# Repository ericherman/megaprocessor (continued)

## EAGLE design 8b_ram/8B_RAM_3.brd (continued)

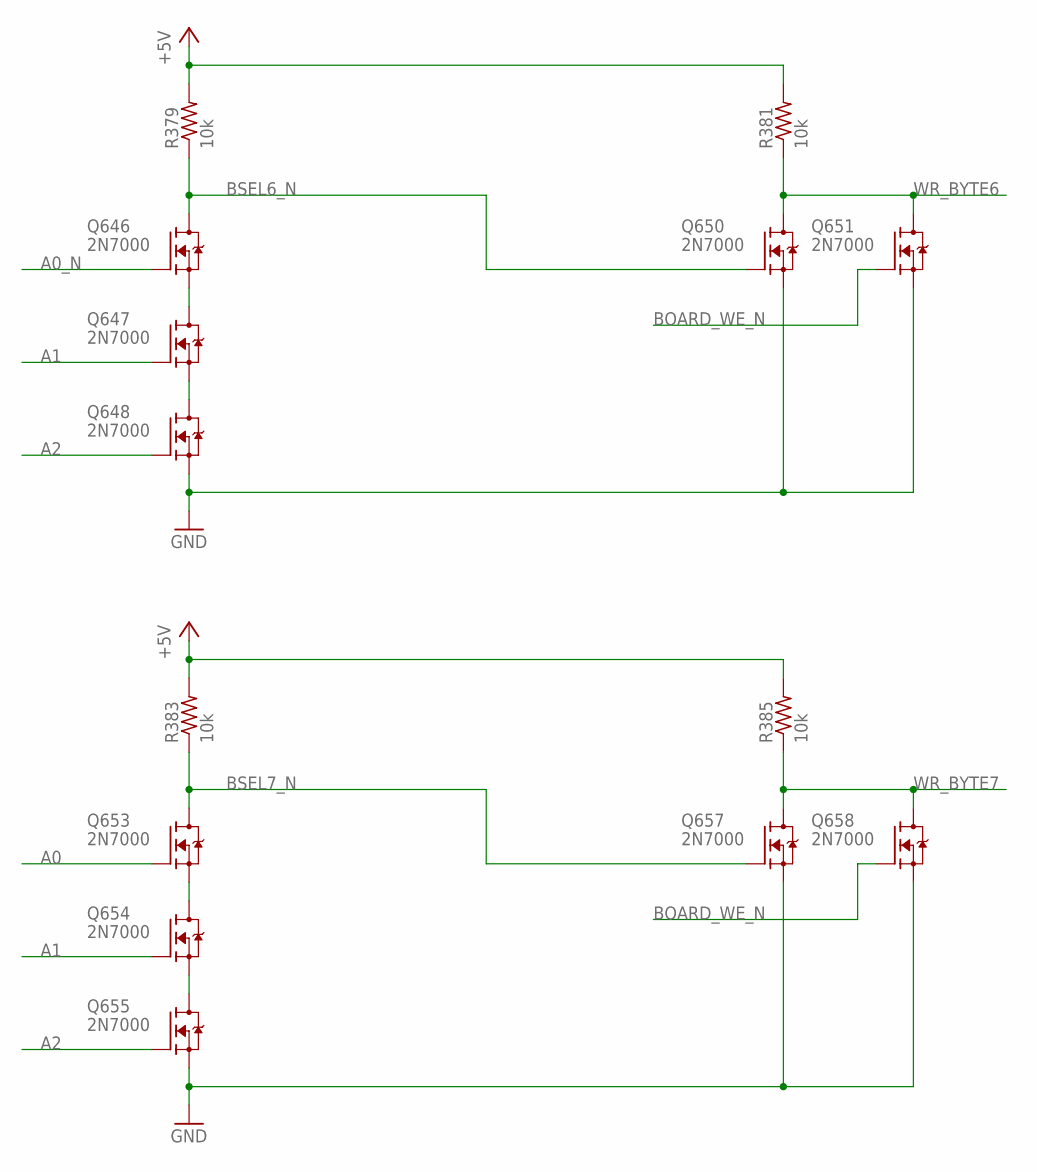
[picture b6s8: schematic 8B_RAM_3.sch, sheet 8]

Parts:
Q646, Q647, Q648, Q650, Q651, Q653, Q654, Q655, Q657, Q658: 2N7000; TO92-DGS
R379, R381, R383, R385: 10k; R_P2INCH

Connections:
+5V: R379.2, R381.2, R383.2, R385.2; also elsewhere on the board
A0: Q653.G; also elsewhere on the board
A0_N: Q646.G; also elsewhere on the board
A1: Q647.G, Q654.G; also elsewhere on the board
A2: Q648.G, Q655.G; also elsewhere on the board
BOARD_WE_N: Q651.G, Q658.G; also elsewhere on the board
BSEL6_N: Q646.D, Q650.G, R379.1; also elsewhere on the board
BSEL7_N: Q653.D, Q657.G, R383.1; also elsewhere on the board
GND: Q648.S, Q650.S, Q651.S, Q655.S, Q657.S, Q658.S; also elsewhere on the board
unnamed: Q646.S, Q647.D
unnamed: Q647.S, Q648.D
unnamed: Q653.S, Q654.D
unnamed: Q654.S, Q655.D
WR_BYTE6: Q650.D, Q651.D, R381.1; also elsewhere on the board
WR_BYTE7: Q657.D, Q658.D, R385.1; also elsewhere on the board

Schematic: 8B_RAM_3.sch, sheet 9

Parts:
D1, D2: L-1334SRT; LED3MM
Q1, Q2, Q3, Q4, Q5, Q6, Q7, Q8, Q9, Q10, Q11, Q12, Q13, Q14, Q15, Q16, Q17, Q18, Q686, Q687: 2N7000; TO92-DGS
R1, R2, R3, R4, R6, R7, R8, R9, R415, R416: 10k; R_P2INCH
R5, R10: 470; R_P2INCH

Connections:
+5V: D1.A, D2.A, R1.2, R2.2, R3.2, R4.2, R6.2, R7.2, R8.2, R9.2, R415.2, R416.2; also elsewhere on the board
B0_0: Q5.G, Q8.D, R4.1, R5.1
B0_0_N: Q6.D, Q8.G, Q17.G, R3.1
B0_1: Q13.G, Q16.D, R9.1, R10.1
B0_1_N: Q14.D, Q16.G, Q18.G, R8.1
BSEL0_N: Q686.G, Q687.G; also elsewhere on the board
GND: Q1.S, Q3.S, Q5.S, Q7.S, Q9.S, Q11.S, Q13.S, Q15.S, Q17.S, Q18.S, Q686.S, Q687.S; also elsewhere on the board
unnamed: Q9.D, Q10.S
unnamed: Q7.D, Q8.S
unnamed: Q11.D, Q12.S
unnamed: Q13.D, Q14.S
unnamed: Q1.D, Q2.S
unnamed: Q3.D, Q4.S
unnamed: Q10.D, Q12.G, Q14.G, R6.1
unnamed: Q5.D, Q6.S
unnamed: Q12.D, Q15.G, R7.1
unnamed: D2.K (C), R10.2
unnamed: Q2.D, Q4.G, Q6.G, R1.1
unnamed: Q4.D, Q7.G, R2.1
unnamed: Q15.D, Q16.S
unnamed: D1.K (C), R5.2
RD_0_0: Q17.D, Q686.D, R415.1; also elsewhere on the board
RD_0_1: Q18.D, Q687.D, R416.1; also elsewhere on the board
WD0: Q2.G; also elsewhere on the board
WD1: Q10.G; also elsewhere on the board
WR_BYTE0: Q1.G, Q3.G, Q9.G, Q11.G; also elsewhere on the board

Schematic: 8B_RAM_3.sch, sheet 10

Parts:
D5, D6: L-1334SRT; LED3MM
Q37, Q38, Q39, Q40, Q41, Q42, Q43, Q44, Q45, Q46, Q47, Q48, Q49, Q50, Q51, Q52, Q53, Q54, Q688, Q689: 2N7000; TO92-DGS
R21, R22, R23, R24, R26, R27, R28, R29, R417, R418: 10k; R_P2INCH
R25, R30: 470; R_P2INCH

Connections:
+5V: D5.A, D6.A, R21.2, R22.2, R23.2, R24.2, R26.2, R27.2, R28.2, R29.2, R417.2, R418.2; also elsewhere on the board
B0_2: Q41.G, Q43.D, R24.1, R25.1
B0_2_N: Q42.D, Q43.G, Q53.G, R23.1
B0_3: Q49.G, Q51.D, R29.1, R30.1
B0_3_N: Q50.D, Q51.G, Q54.G, R28.1
BSEL0_N: Q688.G, Q689.G; also elsewhere on the board
GND: Q37.S, Q39.S, Q41.S, Q44.S, Q45.S, Q47.S, Q49.S, Q52.S, Q53.S, Q54.S, Q688.S, Q689.S; also elsewhere on the board
unnamed: Q37.D, Q38.S
unnamed: Q39.D, Q40.S
unnamed: Q41.D, Q42.S
unnamed: Q38.D, Q40.G, Q42.G, R21.1
unnamed: Q40.D, Q44.G, R22.1
unnamed: D5.K (C), R25.2
unnamed: Q43.S, Q44.D
unnamed: Q45.D, Q46.S
unnamed: Q47.D, Q48.S
unnamed: Q49.D, Q50.S
unnamed: Q46.D, Q48.G, Q50.G, R26.1
unnamed: Q48.D, Q52.G, R27.1
unnamed: D6.K (C), R30.2
unnamed: Q51.S, Q52.D
RD_0_2: Q53.D, Q688.D, R417.1; also elsewhere on the board
RD_0_3: Q54.D, Q689.D, R418.1; also elsewhere on the board
WD2: Q38.G; also elsewhere on the board
WD3: Q46.G; also elsewhere on the board
WR_BYTE0: Q37.G, Q39.G, Q45.G, Q47.G; also elsewhere on the board

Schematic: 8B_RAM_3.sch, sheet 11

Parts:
D7, D8: L-1334SRT; LED3MM
Q55, Q56, Q57, Q58, Q59, Q60, Q61, Q62, Q63, Q64, Q65, Q66, Q67, Q68, Q69, Q70, Q71, Q72, Q690, Q691: 2N7000; TO92-DGS
R31, R32, R33, R34, R36, R37, R38, R39, R419, R420: 10k; R_P2INCH
R35, R40: 470; R_P2INCH

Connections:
+5V: D7.A, D8.A, R31.2, R32.2, R33.2, R34.2, R36.2, R37.2, R38.2, R39.2, R419.2, R420.2; also elsewhere on the board
B0_4: Q59.G, Q61.D, R34.1, R35.1
B0_4_N: Q60.D, Q61.G, Q71.G, R33.1
B0_5: Q67.G, Q69.D, R39.1, R40.1
B0_5_N: Q68.D, Q69.G, Q72.G, R38.1
BSEL0_N: Q690.G, Q691.G; also elsewhere on the board
GND: Q55.S, Q57.S, Q59.S, Q62.S, Q63.S, Q65.S, Q67.S, Q70.S, Q71.S, Q72.S, Q690.S, Q691.S; also elsewhere on the board
unnamed: Q55.D, Q56.S
unnamed: Q57.D, Q58.S
unnamed: Q59.D, Q60.S
unnamed: Q56.D, Q58.G, Q60.G, R31.1
unnamed: Q58.D, Q62.G, R32.1
unnamed: D7.K (C), R35.2
unnamed: Q61.S, Q62.D
unnamed: Q63.D, Q64.S
unnamed: Q65.D, Q66.S
unnamed: Q67.D, Q68.S
unnamed: Q64.D, Q66.G, Q68.G, R36.1
unnamed: Q66.D, Q70.G, R37.1
unnamed: D8.K (C), R40.2
unnamed: Q69.S, Q70.D
RD_0_4: Q71.D, Q691.D, R419.1; also elsewhere on the board
RD_0_5: Q72.D, Q690.D, R420.1; also elsewhere on the board
WD4: Q56.G; also elsewhere on the board
WD5: Q64.G; also elsewhere on the board
WR_BYTE0: Q55.G, Q57.G, Q63.G, Q65.G; also elsewhere on the board

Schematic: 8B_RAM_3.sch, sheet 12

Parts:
D9, D10: L-1334SRT; LED3MM
Q73, Q74, Q75, Q76, Q77, Q78, Q79, Q80, Q81, Q82, Q83, Q84, Q85, Q86, Q87, Q88, Q89, Q90, Q692, Q693: 2N7000; TO92-DGS
R41, R42, R43, R44, R46, R47, R48, R49, R421, R422: 10k; R_P2INCH
R45, R50: 470; R_P2INCH

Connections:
+5V: D9.A, D10.A, R41.2, R42.2, R43.2, R44.2, R46.2, R47.2, R48.2, R49.2, R421.2, R422.2; also elsewhere on the board
B0_6: Q77.G, Q79.D, R44.1, R45.1
B0_6_N: Q78.D, Q79.G, Q89.G, R43.1
B0_7: Q85.G, Q87.D, R49.1, R50.1
B0_7_N: Q86.D, Q87.G, Q90.G, R48.1
BSEL0_N: Q692.G, Q693.G; also elsewhere on the board
GND: Q73.S, Q75.S, Q77.S, Q80.S, Q81.S, Q83.S, Q85.S, Q88.S, Q89.S, Q90.S, Q692.S, Q693.S; also elsewhere on the board
unnamed: Q73.D, Q74.S
unnamed: Q75.D, Q76.S
unnamed: Q77.D, Q78.S
unnamed: Q74.D, Q76.G, Q78.G, R41.1
unnamed: Q76.D, Q80.G, R42.1
unnamed: D9.K (C), R45.2
unnamed: Q79.S, Q80.D
unnamed: Q81.D, Q82.S
unnamed: Q83.D, Q84.S
unnamed: Q85.D, Q86.S
unnamed: Q82.D, Q84.G, Q86.G, R46.1
unnamed: Q84.D, Q88.G, R47.1
unnamed: D10.K (C), R50.2
unnamed: Q87.S, Q88.D
RD_0_6: Q89.D, Q692.D, R421.1; also elsewhere on the board
RD_0_7: Q90.D, Q693.D, R422.1; also elsewhere on the board
WD6: Q74.G; also elsewhere on the board
WD7: Q82.G; also elsewhere on the board
WR_BYTE0: Q73.G, Q75.G, Q81.G, Q83.G; also elsewhere on the board

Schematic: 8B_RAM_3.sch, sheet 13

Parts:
D3, D4: L-1334SRT; LED3MM
Q19, Q20, Q21, Q22, Q23, Q24, Q25, Q26, Q27, Q28, Q29, Q30, Q31, Q32, Q33, Q34, Q35, Q36, Q694, Q695: 2N7000; TO92-DGS
R11, R12, R13, R14, R16, R17, R18, R19, R423, R424: 10k; R_P2INCH
R15, R20: 470; R_P2INCH

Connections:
+5V: D3.A, D4.A, R11.2, R12.2, R13.2, R14.2, R16.2, R17.2, R18.2, R19.2, R423.2, R424.2; also elsewhere on the board
B1_0: Q23.G, Q25.D, R14.1, R15.1
B1_0_N: Q24.D, Q25.G, Q35.G, R13.1
B1_1: Q31.G, Q33.D, R19.1, R20.1
B1_1_N: Q32.D, Q33.G, Q36.G, R18.1
BSEL1_N: Q694.G, Q695.G; also elsewhere on the board
GND: Q19.S, Q21.S, Q23.S, Q26.S, Q27.S, Q29.S, Q31.S, Q34.S, Q35.S, Q36.S, Q694.S, Q695.S; also elsewhere on the board
unnamed: Q19.D, Q20.S
unnamed: Q21.D, Q22.S
unnamed: Q23.D, Q24.S
unnamed: Q20.D, Q22.G, Q24.G, R11.1
unnamed: Q22.D, Q26.G, R12.1
unnamed: D3.K (C), R15.2
unnamed: Q25.S, Q26.D
unnamed: Q27.D, Q28.S
unnamed: Q29.D, Q30.S
unnamed: Q31.D, Q32.S
unnamed: Q28.D, Q30.G, Q32.G, R16.1
unnamed: Q30.D, Q34.G, R17.1
unnamed: D4.K (C), R20.2
unnamed: Q33.S, Q34.D
RD_1_0: Q35.D, Q694.D, R423.1; also elsewhere on the board
RD_1_1: Q36.D, Q695.D, R424.1; also elsewhere on the board
WD0: Q20.G; also elsewhere on the board
WD1: Q28.G; also elsewhere on the board
WR_BYTE1: Q19.G, Q21.G, Q27.G, Q29.G; also elsewhere on the board

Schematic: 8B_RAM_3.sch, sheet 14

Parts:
D11, D12: L-1334SRT; LED3MM
Q91, Q92, Q93, Q94, Q95, Q96, Q97, Q98, Q99, Q100, Q101, Q102, Q103, Q104, Q105, Q106, Q107, Q108, Q696, Q697: 2N7000; TO92-DGS
R51, R52, R53, R54, R56, R57, R58, R59, R425, R426: 10k; R_P2INCH
R55, R60: 470; R_P2INCH

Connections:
+5V: D11.A, D12.A, R51.2, R52.2, R53.2, R54.2, R56.2, R57.2, R58.2, R59.2, R425.2, R426.2; also elsewhere on the board
B1_2: Q95.G, Q97.D, R54.1, R55.1
B1_2_N: Q96.D, Q97.G, Q107.G, R53.1
B1_3: Q103.G, Q105.D, R59.1, R60.1
B1_3_N: Q104.D, Q105.G, Q108.G, R58.1
BSEL1_N: Q696.G, Q697.G; also elsewhere on the board
GND: Q91.S, Q93.S, Q95.S, Q98.S, Q99.S, Q101.S, Q103.S, Q106.S, Q107.S, Q108.S, Q696.S, Q697.S; also elsewhere on the board
unnamed: Q91.D, Q92.S
unnamed: Q93.D, Q94.S
unnamed: Q95.D, Q96.S
unnamed: Q92.D, Q94.G, Q96.G, R51.1
unnamed: Q94.D, Q98.G, R52.1
unnamed: D11.K (C), R55.2
unnamed: Q97.S, Q98.D
unnamed: Q99.D, Q100.S
unnamed: Q101.D, Q102.S
unnamed: Q103.D, Q104.S
unnamed: Q100.D, Q102.G, Q104.G, R56.1
unnamed: Q102.D, Q106.G, R57.1
unnamed: D12.K (C), R60.2
unnamed: Q105.S, Q106.D
RD_1_2: Q107.D, Q697.D, R425.1; also elsewhere on the board
RD_1_3: Q108.D, Q696.D, R426.1; also elsewhere on the board
WD2: Q92.G; also elsewhere on the board
WD3: Q100.G; also elsewhere on the board
WR_BYTE1: Q91.G, Q93.G, Q99.G, Q101.G; also elsewhere on the board

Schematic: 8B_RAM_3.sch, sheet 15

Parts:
D13, D14: L-1334SRT; LED3MM
Q109, Q110, Q111, Q112, Q113, Q114, Q115, Q116, Q117, Q118, Q119, Q120, Q121, Q122, Q123, Q124, Q125, Q126, Q698, Q699: 2N7000; TO92-DGS
R61, R62, R63, R64, R66, R67, R68, R69, R427, R428: 10k; R_P2INCH
R65, R70: 470; R_P2INCH

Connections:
+5V: D13.A, D14.A, R61.2, R62.2, R63.2, R64.2, R66.2, R67.2, R68.2, R69.2, R427.2, R428.2; also elsewhere on the board
B1_4: Q113.G, Q115.D, R64.1, R65.1
B1_4_N: Q114.D, Q115.G, Q125.G, R63.1
B1_5: Q121.G, Q123.D, R69.1, R70.1
B1_5_N: Q122.D, Q123.G, Q126.G, R68.1
BSEL1_N: Q698.G, Q699.G; also elsewhere on the board
GND: Q109.S, Q111.S, Q113.S, Q116.S, Q117.S, Q119.S, Q121.S, Q124.S, Q125.S, Q126.S, Q698.S, Q699.S; also elsewhere on the board
unnamed: Q109.D, Q110.S
unnamed: Q111.D, Q112.S
unnamed: Q113.D, Q114.S
unnamed: Q110.D, Q112.G, Q114.G, R61.1
unnamed: Q112.D, Q116.G, R62.1
unnamed: D13.K (C), R65.2
unnamed: Q115.S, Q116.D
unnamed: Q117.D, Q118.S
unnamed: Q119.D, Q120.S
unnamed: Q121.D, Q122.S
unnamed: Q118.D, Q120.G, Q122.G, R66.1
unnamed: Q120.D, Q124.G, R67.1
unnamed: D14.K (C), R70.2
unnamed: Q123.S, Q124.D
RD_1_4: Q125.D, Q698.D, R427.1; also elsewhere on the board
RD_1_5: Q126.D, Q699.D, R428.1; also elsewhere on the board
WD4: Q110.G; also elsewhere on the board
WD5: Q118.G; also elsewhere on the board
WR_BYTE1: Q109.G, Q111.G, Q117.G, Q119.G; also elsewhere on the board

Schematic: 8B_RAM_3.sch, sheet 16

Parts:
D15, D16: L-1334SRT; LED3MM
Q127, Q128, Q129, Q130, Q131, Q132, Q133, Q134, Q135, Q136, Q137, Q138, Q139, Q140, Q141, Q142, Q143, Q144, Q700, Q701: 2N7000; TO92-DGS
R71, R72, R73, R74, R76, R77, R78, R79, R429, R430: 10k; R_P2INCH
R75, R80: 470; R_P2INCH

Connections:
+5V: D15.A, D16.A, R71.2, R72.2, R73.2, R74.2, R76.2, R77.2, R78.2, R79.2, R429.2, R430.2; also elsewhere on the board
B1_6: Q131.G, Q133.D, R74.1, R75.1
B1_6_N: Q132.D, Q133.G, Q143.G, R73.1
B1_7: Q139.G, Q141.D, R79.1, R80.1
B1_7_N: Q140.D, Q141.G, Q144.G, R78.1
BSEL1_N: Q700.G, Q701.G; also elsewhere on the board
GND: Q127.S, Q129.S, Q131.S, Q134.S, Q135.S, Q137.S, Q139.S, Q142.S, Q143.S, Q144.S, Q700.S, Q701.S; also elsewhere on the board
unnamed: Q127.D, Q128.S
unnamed: Q129.D, Q130.S
unnamed: Q131.D, Q132.S
unnamed: Q128.D, Q130.G, Q132.G, R71.1
unnamed: Q130.D, Q134.G, R72.1
unnamed: D15.K (C), R75.2
unnamed: Q133.S, Q134.D
unnamed: Q135.D, Q136.S
unnamed: Q137.D, Q138.S
unnamed: Q139.D, Q140.S
unnamed: Q136.D, Q138.G, Q140.G, R76.1
unnamed: Q138.D, Q142.G, R77.1
unnamed: D16.K (C), R80.2
unnamed: Q141.S, Q142.D
RD_1_6: Q143.D, Q700.D, R429.1; also elsewhere on the board
RD_1_7: Q144.D, Q701.D, R430.1; also elsewhere on the board
WD6: Q128.G; also elsewhere on the board
WD7: Q136.G; also elsewhere on the board
WR_BYTE1: Q127.G, Q129.G, Q135.G, Q137.G; also elsewhere on the board

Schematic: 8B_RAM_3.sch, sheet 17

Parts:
D17, D18: L-1334SRT; LED3MM
Q145, Q146, Q147, Q148, Q149, Q150, Q151, Q152, Q153, Q154, Q155, Q156, Q157, Q158, Q159, Q160, Q161, Q162, Q702, Q703: 2N7000; TO92-DGS
R81, R82, R83, R84, R86, R87, R88, R89, R431, R432: 10k; R_P2INCH
R85, R90: 470; R_P2INCH

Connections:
+5V: D17.A, D18.A, R81.2, R82.2, R83.2, R84.2, R86.2, R87.2, R88.2, R89.2, R431.2, R432.2; also elsewhere on the board
B2_0: Q149.G, Q151.D, R84.1, R85.1
B2_0_N: Q150.D, Q151.G, Q161.G, R83.1
B2_1: Q157.G, Q159.D, R89.1, R90.1
B2_1_N: Q158.D, Q159.G, Q162.G, R88.1
BSEL2_N: Q702.G, Q703.G; also elsewhere on the board
GND: Q145.S, Q147.S, Q149.S, Q152.S, Q153.S, Q155.S, Q157.S, Q160.S, Q161.S, Q162.S, Q702.S, Q703.S; also elsewhere on the board
unnamed: Q145.D, Q146.S
unnamed: Q147.D, Q148.S
unnamed: Q149.D, Q150.S
unnamed: Q146.D, Q148.G, Q150.G, R81.1
unnamed: Q148.D, Q152.G, R82.1
unnamed: D17.K (C), R85.2
unnamed: Q151.S, Q152.D
unnamed: Q153.D, Q154.S
unnamed: Q155.D, Q156.S
unnamed: Q157.D, Q158.S
unnamed: Q154.D, Q156.G, Q158.G, R86.1
unnamed: Q156.D, Q160.G, R87.1
unnamed: D18.K (C), R90.2
unnamed: Q159.S, Q160.D
RD_2_0: Q161.D, Q702.D, R431.1; also elsewhere on the board
RD_2_1: Q162.D, Q703.D, R432.1; also elsewhere on the board
WD0: Q146.G; also elsewhere on the board
WD1: Q154.G; also elsewhere on the board
WR_BYTE2: Q145.G, Q147.G, Q153.G, Q155.G; also elsewhere on the board

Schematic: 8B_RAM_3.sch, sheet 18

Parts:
D19, D20: L-1334SRT; LED3MM
Q163, Q164, Q165, Q166, Q167, Q168, Q169, Q170, Q171, Q172, Q173, Q174, Q175, Q176, Q177, Q178, Q179, Q180, Q704, Q705: 2N7000; TO92-DGS
R91, R92, R93, R94, R96, R97, R98, R99, R433, R434: 10k; R_P2INCH
R95, R100: 470; R_P2INCH

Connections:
+5V: D19.A, D20.A, R91.2, R92.2, R93.2, R94.2, R96.2, R97.2, R98.2, R99.2, R433.2, R434.2; also elsewhere on the board
B2_2: Q167.G, Q169.D, R94.1, R95.1
B2_2_N: Q168.D, Q169.G, Q179.G, R93.1
B2_3: Q175.G, Q177.D, R99.1, R100.1
B2_3_N: Q176.D, Q177.G, Q180.G, R98.1
BSEL2_N: Q704.G, Q705.G; also elsewhere on the board
GND: Q163.S, Q165.S, Q167.S, Q170.S, Q171.S, Q173.S, Q175.S, Q178.S, Q179.S, Q180.S, Q704.S, Q705.S; also elsewhere on the board
unnamed: Q163.D, Q164.S
unnamed: Q165.D, Q166.S
unnamed: Q167.D, Q168.S
unnamed: Q164.D, Q166.G, Q168.G, R91.1
unnamed: Q166.D, Q170.G, R92.1
unnamed: D19.K (C), R95.2
unnamed: Q169.S, Q170.D
unnamed: Q171.D, Q172.S
unnamed: Q173.D, Q174.S
unnamed: Q175.D, Q176.S
unnamed: Q172.D, Q174.G, Q176.G, R96.1
unnamed: Q174.D, Q178.G, R97.1
unnamed: D20.K (C), R100.2
unnamed: Q177.S, Q178.D
RD_2_2: Q179.D, Q704.D, R433.1; also elsewhere on the board
RD_2_3: Q180.D, Q705.D, R434.1; also elsewhere on the board
WD2: Q164.G; also elsewhere on the board
WD3: Q172.G; also elsewhere on the board
WR_BYTE2: Q163.G, Q165.G, Q171.G, Q173.G; also elsewhere on the board

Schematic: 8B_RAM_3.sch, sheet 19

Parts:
D21, D22: L-1334SRT; LED3MM
Q181, Q182, Q183, Q184, Q185, Q186, Q187, Q188, Q189, Q190, Q191, Q192, Q193, Q194, Q195, Q196, Q197, Q198, Q706, Q707: 2N7000; TO92-DGS
R101, R102, R103, R104, R106, R107, R108, R109, R435, R436: 10k; R_P2INCH
R105, R110: 470; R_P2INCH

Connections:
+5V: D21.A, D22.A, R101.2, R102.2, R103.2, R104.2, R106.2, R107.2, R108.2, R109.2, R435.2, R436.2; also elsewhere on the board
B2_4: Q185.G, Q187.D, R104.1, R105.1
B2_4_N: Q186.D, Q187.G, Q197.G, R103.1
B2_5: Q193.G, Q195.D, R109.1, R110.1
B2_5_N: Q194.D, Q195.G, Q198.G, R108.1
BSEL2_N: Q706.G, Q707.G; also elsewhere on the board
GND: Q181.S, Q183.S, Q185.S, Q188.S, Q189.S, Q191.S, Q193.S, Q196.S, Q197.S, Q198.S, Q706.S, Q707.S; also elsewhere on the board
unnamed: Q181.D, Q182.S
unnamed: Q183.D, Q184.S
unnamed: Q185.D, Q186.S
unnamed: Q182.D, Q184.G, Q186.G, R101.1
unnamed: Q184.D, Q188.G, R102.1
unnamed: D21.K (C), R105.2
unnamed: Q187.S, Q188.D
unnamed: Q189.D, Q190.S
unnamed: Q191.D, Q192.S
unnamed: Q193.D, Q194.S
unnamed: Q190.D, Q192.G, Q194.G, R106.1
unnamed: Q192.D, Q196.G, R107.1
unnamed: D22.K (C), R110.2
unnamed: Q195.S, Q196.D
RD_2_4: Q197.D, Q706.D, R435.1; also elsewhere on the board
RD_2_5: Q198.D, Q707.D, R436.1; also elsewhere on the board
WD4: Q182.G; also elsewhere on the board
WD5: Q190.G; also elsewhere on the board
WR_BYTE2: Q181.G, Q183.G, Q189.G, Q191.G; also elsewhere on the board

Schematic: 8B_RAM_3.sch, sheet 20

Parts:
D23, D24: L-1334SRT; LED3MM
Q199, Q200, Q201, Q202, Q203, Q204, Q205, Q206, Q207, Q208, Q209, Q210, Q211, Q212, Q213, Q214, Q215, Q216, Q708, Q709: 2N7000; TO92-DGS
R111, R112, R113, R114, R116, R117, R118, R119, R437, R438: 10k; R_P2INCH
R115, R120: 470; R_P2INCH

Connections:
+5V: D23.A, D24.A, R111.2, R112.2, R113.2, R114.2, R116.2, R117.2, R118.2, R119.2, R437.2, R438.2; also elsewhere on the board
B2_6: Q203.G, Q205.D, R114.1, R115.1
B2_6_N: Q204.D, Q205.G, Q215.G, R113.1
B2_7: Q211.G, Q213.D, R119.1, R120.1
B2_7_N: Q212.D, Q213.G, Q216.G, R118.1
BSEL2_N: Q708.G, Q709.G; also elsewhere on the board
GND: Q199.S, Q201.S, Q203.S, Q206.S, Q207.S, Q209.S, Q211.S, Q214.S, Q215.S, Q216.S, Q708.S, Q709.S; also elsewhere on the board
unnamed: Q199.D, Q200.S
unnamed: Q201.D, Q202.S
unnamed: Q203.D, Q204.S
unnamed: Q200.D, Q202.G, Q204.G, R111.1
unnamed: Q202.D, Q206.G, R112.1
unnamed: D23.K (C), R115.2
unnamed: Q205.S, Q206.D
unnamed: Q207.D, Q208.S
unnamed: Q209.D, Q210.S
unnamed: Q211.D, Q212.S
unnamed: Q208.D, Q210.G, Q212.G, R116.1
unnamed: Q210.D, Q214.G, R117.1
unnamed: D24.K (C), R120.2
unnamed: Q213.S, Q214.D
RD_2_6: Q215.D, Q708.D, R437.1; also elsewhere on the board
RD_2_7: Q216.D, Q709.D, R438.1; also elsewhere on the board
WD6: Q200.G; also elsewhere on the board
WD7: Q208.G; also elsewhere on the board
WR_BYTE2: Q199.G, Q201.G, Q207.G, Q209.G; also elsewhere on the board

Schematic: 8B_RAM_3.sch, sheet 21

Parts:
D25, D26: L-1334SRT; LED3MM
Q217, Q218, Q219, Q220, Q221, Q222, Q223, Q224, Q225, Q226, Q227, Q228, Q229, Q230, Q231, Q232, Q233, Q234, Q710, Q711: 2N7000; TO92-DGS
R121, R122, R123, R124, R126, R127, R128, R129, R439, R440: 10k; R_P2INCH
R125, R130: 470; R_P2INCH

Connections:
+5V: D25.A, D26.A, R121.2, R122.2, R123.2, R124.2, R126.2, R127.2, R128.2, R129.2, R439.2, R440.2; also elsewhere on the board
B3_0: Q221.G, Q223.D, R124.1, R125.1
B3_0_N: Q222.D, Q223.G, Q233.G, R123.1
B3_1: Q229.G, Q231.D, R129.1, R130.1
B3_1_N: Q230.D, Q231.G, Q234.G, R128.1
BSEL3_N: Q710.G, Q711.G; also elsewhere on the board
GND: Q217.S, Q219.S, Q221.S, Q224.S, Q225.S, Q227.S, Q229.S, Q232.S, Q233.S, Q234.S, Q710.S, Q711.S; also elsewhere on the board
unnamed: Q217.D, Q218.S
unnamed: Q219.D, Q220.S
unnamed: Q221.D, Q222.S
unnamed: Q218.D, Q220.G, Q222.G, R121.1
unnamed: Q220.D, Q224.G, R122.1
unnamed: D25.K (C), R125.2
unnamed: Q223.S, Q224.D
unnamed: Q225.D, Q226.S
unnamed: Q227.D, Q228.S
unnamed: Q229.D, Q230.S
unnamed: Q226.D, Q228.G, Q230.G, R126.1
unnamed: Q228.D, Q232.G, R127.1
unnamed: D26.K (C), R130.2
unnamed: Q231.S, Q232.D
RD_3_0: Q233.D, Q710.D, R439.1; also elsewhere on the board
RD_3_1: Q234.D, Q711.D, R440.1; also elsewhere on the board
WD0: Q218.G; also elsewhere on the board
WD1: Q226.G; also elsewhere on the board
WR_BYTE3: Q217.G, Q219.G, Q225.G, Q227.G; also elsewhere on the board

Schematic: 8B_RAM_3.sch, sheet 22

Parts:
D27, D28: L-1334SRT; LED3MM
Q235, Q236, Q237, Q238, Q239, Q240, Q241, Q242, Q243, Q244, Q245, Q246, Q247, Q248, Q249, Q250, Q251, Q252, Q712, Q713: 2N7000; TO92-DGS
R131, R132, R133, R134, R136, R137, R138, R139, R441, R442: 10k; R_P2INCH
R135, R140: 470; R_P2INCH

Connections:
+5V: D27.A, D28.A, R131.2, R132.2, R133.2, R134.2, R136.2, R137.2, R138.2, R139.2, R441.2, R442.2; also elsewhere on the board
B3_2: Q239.G, Q241.D, R134.1, R135.1
B3_2_N: Q240.D, Q241.G, Q251.G, R133.1
B3_3: Q247.G, Q249.D, R139.1, R140.1
B3_3_N: Q248.D, Q249.G, Q252.G, R138.1
BSEL3_N: Q712.G, Q713.G; also elsewhere on the board
GND: Q235.S, Q237.S, Q239.S, Q242.S, Q243.S, Q245.S, Q247.S, Q250.S, Q251.S, Q252.S, Q712.S, Q713.S; also elsewhere on the board
unnamed: Q235.D, Q236.S
unnamed: Q237.D, Q238.S
unnamed: Q239.D, Q240.S
unnamed: Q236.D, Q238.G, Q240.G, R131.1
unnamed: Q238.D, Q242.G, R132.1
unnamed: D27.K (C), R135.2
unnamed: Q241.S, Q242.D
unnamed: Q243.D, Q244.S
unnamed: Q245.D, Q246.S
unnamed: Q247.D, Q248.S
unnamed: Q244.D, Q246.G, Q248.G, R136.1
unnamed: Q246.D, Q250.G, R137.1
unnamed: D28.K (C), R140.2
unnamed: Q249.S, Q250.D
RD_3_2: Q251.D, Q712.D, R441.1; also elsewhere on the board
RD_3_3: Q252.D, Q713.D, R442.1; also elsewhere on the board
WD2: Q236.G; also elsewhere on the board
WD3: Q244.G; also elsewhere on the board
WR_BYTE3: Q235.G, Q237.G, Q243.G, Q245.G; also elsewhere on the board

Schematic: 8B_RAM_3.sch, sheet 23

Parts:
D29, D30: L-1334SRT; LED3MM
Q253, Q254, Q255, Q256, Q257, Q258, Q259, Q260, Q261, Q262, Q263, Q264, Q265, Q266, Q267, Q268, Q269, Q270, Q714, Q715: 2N7000; TO92-DGS
R141, R142, R143, R144, R146, R147, R148, R149, R443, R444: 10k; R_P2INCH
R145, R150: 470; R_P2INCH

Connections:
+5V: D29.A, D30.A, R141.2, R142.2, R143.2, R144.2, R146.2, R147.2, R148.2, R149.2, R443.2, R444.2; also elsewhere on the board
B3_4: Q257.G, Q259.D, R144.1, R145.1
B3_4_N: Q258.D, Q259.G, Q269.G, R143.1
B3_5: Q265.G, Q267.D, R149.1, R150.1
B3_5_N: Q266.D, Q267.G, Q270.G, R148.1
BSEL3_N: Q714.G, Q715.G; also elsewhere on the board
GND: Q253.S, Q255.S, Q257.S, Q260.S, Q261.S, Q263.S, Q265.S, Q268.S, Q269.S, Q270.S, Q714.S, Q715.S; also elsewhere on the board
unnamed: Q253.D, Q254.S
unnamed: Q255.D, Q256.S
unnamed: Q257.D, Q258.S
unnamed: Q254.D, Q256.G, Q258.G, R141.1
unnamed: Q256.D, Q260.G, R142.1
unnamed: D29.K (C), R145.2
unnamed: Q259.S, Q260.D
unnamed: Q261.D, Q262.S
unnamed: Q263.D, Q264.S
unnamed: Q265.D, Q266.S
unnamed: Q262.D, Q264.G, Q266.G, R146.1
unnamed: Q264.D, Q268.G, R147.1
unnamed: D30.K (C), R150.2
unnamed: Q267.S, Q268.D
RD_3_4: Q269.D, Q714.D, R443.1; also elsewhere on the board
RD_3_5: Q270.D, Q715.D, R444.1; also elsewhere on the board
WD4: Q254.G; also elsewhere on the board
WD5: Q262.G; also elsewhere on the board
WR_BYTE3: Q253.G, Q255.G, Q261.G, Q263.G; also elsewhere on the board

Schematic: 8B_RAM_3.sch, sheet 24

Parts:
D31, D32: L-1334SRT; LED3MM
Q271, Q272, Q273, Q274, Q275, Q276, Q277, Q278, Q279, Q280, Q281, Q282, Q283, Q284, Q285, Q286, Q287, Q288, Q716, Q717: 2N7000; TO92-DGS
R151, R152, R153, R154, R156, R157, R158, R159, R445, R446: 10k; R_P2INCH
R155, R160: 470; R_P2INCH

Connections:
+5V: D31.A, D32.A, R151.2, R152.2, R153.2, R154.2, R156.2, R157.2, R158.2, R159.2, R445.2, R446.2; also elsewhere on the board
B3_6: Q275.G, Q277.D, R154.1, R155.1
B3_6_N: Q276.D, Q277.G, Q287.G, R153.1
B3_7: Q283.G, Q285.D, R159.1, R160.1
B3_7_N: Q284.D, Q285.G, Q288.G, R158.1
BSEL3_N: Q716.G, Q717.G; also elsewhere on the board
GND: Q271.S, Q273.S, Q275.S, Q278.S, Q279.S, Q281.S, Q283.S, Q286.S, Q287.S, Q288.S, Q716.S, Q717.S; also elsewhere on the board
unnamed: Q271.D, Q272.S
unnamed: Q273.D, Q274.S
unnamed: Q275.D, Q276.S
unnamed: Q272.D, Q274.G, Q276.G, R151.1
unnamed: Q274.D, Q278.G, R152.1
unnamed: D31.K (C), R155.2
unnamed: Q277.S, Q278.D
unnamed: Q279.D, Q280.S
unnamed: Q281.D, Q282.S
unnamed: Q283.D, Q284.S
unnamed: Q280.D, Q282.G, Q284.G, R156.1
unnamed: Q282.D, Q286.G, R157.1
unnamed: D32.K (C), R160.2
unnamed: Q285.S, Q286.D
RD_3_6: Q287.D, Q716.D, R445.1; also elsewhere on the board
RD_3_7: Q288.D, Q717.D, R446.1; also elsewhere on the board
WD6: Q272.G; also elsewhere on the board
WD7: Q280.G; also elsewhere on the board
WR_BYTE3: Q271.G, Q273.G, Q279.G, Q281.G; also elsewhere on the board

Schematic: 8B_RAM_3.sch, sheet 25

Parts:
D33, D34: L-1334SRT; LED3MM
Q289, Q290, Q291, Q292, Q293, Q294, Q295, Q296, Q297, Q298, Q299, Q300, Q301, Q302, Q303, Q304, Q305, Q306, Q718, Q719: 2N7000; TO92-DGS
R161, R162, R163, R164, R166, R167, R168, R169, R447, R448: 10k; R_P2INCH
R165, R170: 470; R_P2INCH

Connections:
+5V: D33.A, D34.A, R161.2, R162.2, R163.2, R164.2, R166.2, R167.2, R168.2, R169.2, R447.2, R448.2; also elsewhere on the board
B4_0: Q293.G, Q295.D, R164.1, R165.1
B4_0_N: Q294.D, Q295.G, Q305.G, R163.1
B4_1: Q301.G, Q303.D, R169.1, R170.1
B4_1_N: Q302.D, Q303.G, Q306.G, R168.1
BSEL4_N: Q718.G, Q719.G; also elsewhere on the board
GND: Q289.S, Q291.S, Q293.S, Q296.S, Q297.S, Q299.S, Q301.S, Q304.S, Q305.S, Q306.S, Q718.S, Q719.S; also elsewhere on the board
unnamed: Q289.D, Q290.S
unnamed: Q291.D, Q292.S
unnamed: Q293.D, Q294.S
unnamed: Q290.D, Q292.G, Q294.G, R161.1
unnamed: Q292.D, Q296.G, R162.1
unnamed: D33.K (C), R165.2
unnamed: Q295.S, Q296.D
unnamed: Q297.D, Q298.S
unnamed: Q299.D, Q300.S
unnamed: Q301.D, Q302.S
unnamed: Q298.D, Q300.G, Q302.G, R166.1
unnamed: Q300.D, Q304.G, R167.1
unnamed: D34.K (C), R170.2
unnamed: Q303.S, Q304.D
RD_4_0: Q305.D, Q718.D, R447.1; also elsewhere on the board
RD_4_1: Q306.D, Q719.D, R448.1; also elsewhere on the board
WD0: Q290.G; also elsewhere on the board
WD1: Q298.G; also elsewhere on the board
WR_BYTE4: Q289.G, Q291.G, Q297.G, Q299.G; also elsewhere on the board

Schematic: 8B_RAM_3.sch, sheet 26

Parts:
D35, D36: L-1334SRT; LED3MM
Q307, Q308, Q309, Q310, Q311, Q312, Q313, Q314, Q315, Q316, Q317, Q318, Q319, Q320, Q321, Q322, Q323, Q324, Q720, Q721: 2N7000; TO92-DGS
R171, R172, R173, R174, R176, R177, R178, R179, R449, R450: 10k; R_P2INCH
R175, R180: 470; R_P2INCH

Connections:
+5V: D35.A, D36.A, R171.2, R172.2, R173.2, R174.2, R176.2, R177.2, R178.2, R179.2, R449.2, R450.2; also elsewhere on the board
B4_2: Q311.G, Q313.D, R174.1, R175.1
B4_2_N: Q312.D, Q313.G, Q323.G, R173.1
B4_3: Q319.G, Q321.D, R179.1, R180.1
B4_3_N: Q320.D, Q321.G, Q324.G, R178.1
BSEL4_N: Q720.G, Q721.G; also elsewhere on the board
GND: Q307.S, Q309.S, Q311.S, Q314.S, Q315.S, Q317.S, Q319.S, Q322.S, Q323.S, Q324.S, Q720.S, Q721.S; also elsewhere on the board
unnamed: Q307.D, Q308.S
unnamed: Q309.D, Q310.S
unnamed: Q311.D, Q312.S
unnamed: Q308.D, Q310.G, Q312.G, R171.1
unnamed: Q310.D, Q314.G, R172.1
unnamed: D35.K (C), R175.2
unnamed: Q313.S, Q314.D
unnamed: Q315.D, Q316.S
unnamed: Q317.D, Q318.S
unnamed: Q319.D, Q320.S
unnamed: Q316.D, Q318.G, Q320.G, R176.1
unnamed: Q318.D, Q322.G, R177.1
unnamed: D36.K (C), R180.2
unnamed: Q321.S, Q322.D
RD_4_2: Q323.D, Q720.D, R449.1; also elsewhere on the board
RD_4_3: Q324.D, Q721.D, R450.1; also elsewhere on the board
WD2: Q308.G; also elsewhere on the board
WD3: Q316.G; also elsewhere on the board
WR_BYTE4: Q307.G, Q309.G, Q315.G, Q317.G; also elsewhere on the board

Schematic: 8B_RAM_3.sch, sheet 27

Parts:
D37, D38: L-1334SRT; LED3MM
Q325, Q326, Q327, Q328, Q329, Q330, Q331, Q332, Q333, Q334, Q335, Q336, Q337, Q338, Q339, Q340, Q341, Q342, Q722, Q723: 2N7000; TO92-DGS
R181, R182, R183, R184, R186, R187, R188, R189, R451, R452: 10k; R_P2INCH
R185, R190: 470; R_P2INCH

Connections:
+5V: D37.A, D38.A, R181.2, R182.2, R183.2, R184.2, R186.2, R187.2, R188.2, R189.2, R451.2, R452.2; also elsewhere on the board
B4_4: Q329.G, Q331.D, R184.1, R185.1
B4_4_N: Q330.D, Q331.G, Q341.G, R183.1
B4_5: Q337.G, Q339.D, R189.1, R190.1
B4_5_N: Q338.D, Q339.G, Q342.G, R188.1
BSEL4_N: Q722.G, Q723.G; also elsewhere on the board
GND: Q325.S, Q327.S, Q329.S, Q332.S, Q333.S, Q335.S, Q337.S, Q340.S, Q341.S, Q342.S, Q722.S, Q723.S; also elsewhere on the board
unnamed: Q325.D, Q326.S
unnamed: Q327.D, Q328.S
unnamed: Q329.D, Q330.S
unnamed: Q326.D, Q328.G, Q330.G, R181.1
unnamed: Q328.D, Q332.G, R182.1
unnamed: D37.K (C), R185.2
unnamed: Q331.S, Q332.D
unnamed: Q333.D, Q334.S
unnamed: Q335.D, Q336.S
unnamed: Q337.D, Q338.S
unnamed: Q334.D, Q336.G, Q338.G, R186.1
unnamed: Q336.D, Q340.G, R187.1
unnamed: D38.K (C), R190.2
unnamed: Q339.S, Q340.D
RD_4_4: Q341.D, Q722.D, R451.1; also elsewhere on the board
RD_4_5: Q342.D, Q723.D, R452.1; also elsewhere on the board
WD4: Q326.G; also elsewhere on the board
WD5: Q334.G; also elsewhere on the board
WR_BYTE4: Q325.G, Q327.G, Q333.G, Q335.G; also elsewhere on the board

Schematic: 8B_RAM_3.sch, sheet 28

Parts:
D39, D40: L-1334SRT; LED3MM
Q343, Q344, Q345, Q346, Q347, Q348, Q349, Q350, Q351, Q352, Q353, Q354, Q355, Q356, Q357, Q358, Q359, Q360, Q724, Q725: 2N7000; TO92-DGS
R191, R192, R193, R194, R196, R197, R198, R199, R453, R454: 10k; R_P2INCH
R195, R200: 470; R_P2INCH

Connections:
+5V: D39.A, D40.A, R191.2, R192.2, R193.2, R194.2, R196.2, R197.2, R198.2, R199.2, R453.2, R454.2; also elsewhere on the board
B4_6: Q347.G, Q349.D, R194.1, R195.1
B4_6_N: Q348.D, Q349.G, Q359.G, R193.1
B4_7: Q355.G, Q357.D, R199.1, R200.1
B4_7_N: Q356.D, Q357.G, Q360.G, R198.1
BSEL4_N: Q724.G, Q725.G; also elsewhere on the board
GND: Q343.S, Q345.S, Q347.S, Q350.S, Q351.S, Q353.S, Q355.S, Q358.S, Q359.S, Q360.S, Q724.S, Q725.S; also elsewhere on the board
unnamed: Q343.D, Q344.S
unnamed: Q345.D, Q346.S
unnamed: Q347.D, Q348.S
unnamed: Q344.D, Q346.G, Q348.G, R191.1
unnamed: Q346.D, Q350.G, R192.1
unnamed: D39.K (C), R195.2
unnamed: Q349.S, Q350.D
unnamed: Q351.D, Q352.S
unnamed: Q353.D, Q354.S
unnamed: Q355.D, Q356.S
unnamed: Q352.D, Q354.G, Q356.G, R196.1
unnamed: Q354.D, Q358.G, R197.1
unnamed: D40.K (C), R200.2
unnamed: Q357.S, Q358.D
RD_4_6: Q359.D, Q724.D, R453.1; also elsewhere on the board
RD_4_7: Q360.D, Q725.D, R454.1; also elsewhere on the board
WD6: Q344.G; also elsewhere on the board
WD7: Q352.G; also elsewhere on the board
WR_BYTE4: Q343.G, Q345.G, Q351.G, Q353.G; also elsewhere on the board

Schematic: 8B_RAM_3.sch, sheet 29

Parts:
D41, D42: L-1334SRT; LED3MM
Q361, Q362, Q363, Q364, Q365, Q366, Q367, Q368, Q369, Q370, Q371, Q372, Q373, Q374, Q375, Q376, Q377, Q378, Q726, Q727: 2N7000; TO92-DGS
R201, R202, R203, R204, R206, R207, R208, R209, R455, R456: 10k; R_P2INCH
R205, R210: 470; R_P2INCH

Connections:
+5V: D41.A, D42.A, R201.2, R202.2, R203.2, R204.2, R206.2, R207.2, R208.2, R209.2, R455.2, R456.2; also elsewhere on the board
B5_0: Q365.G, Q367.D, R204.1, R205.1
B5_0_N: Q366.D, Q367.G, Q377.G, R203.1
B5_1: Q373.G, Q375.D, R209.1, R210.1
B5_1_N: Q374.D, Q375.G, Q378.G, R208.1
BSEL5_N: Q726.G, Q727.G; also elsewhere on the board
GND: Q361.S, Q363.S, Q365.S, Q368.S, Q369.S, Q371.S, Q373.S, Q376.S, Q377.S, Q378.S, Q726.S, Q727.S; also elsewhere on the board
unnamed: Q361.D, Q362.S
unnamed: Q363.D, Q364.S
unnamed: Q365.D, Q366.S
unnamed: Q362.D, Q364.G, Q366.G, R201.1
unnamed: Q364.D, Q368.G, R202.1
unnamed: D41.K (C), R205.2
unnamed: Q367.S, Q368.D
unnamed: Q369.D, Q370.S
unnamed: Q371.D, Q372.S
unnamed: Q373.D, Q374.S
unnamed: Q370.D, Q372.G, Q374.G, R206.1
unnamed: Q372.D, Q376.G, R207.1
unnamed: D42.K (C), R210.2
unnamed: Q375.S, Q376.D
RD_5_0: Q377.D, Q726.D, R455.1; also elsewhere on the board
RD_5_1: Q378.D, Q727.D, R456.1; also elsewhere on the board
WD0: Q362.G; also elsewhere on the board
WD1: Q370.G; also elsewhere on the board
WR_BYTE5: Q361.G, Q363.G, Q369.G, Q371.G; also elsewhere on the board

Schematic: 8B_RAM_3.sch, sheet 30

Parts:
D43, D44: L-1334SRT; LED3MM
Q379, Q380, Q381, Q382, Q383, Q384, Q385, Q386, Q387, Q388, Q389, Q390, Q391, Q392, Q393, Q394, Q395, Q396, Q728, Q729: 2N7000; TO92-DGS
R211, R212, R213, R214, R216, R217, R218, R219, R457, R458: 10k; R_P2INCH
R215, R220: 470; R_P2INCH

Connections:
+5V: D43.A, D44.A, R211.2, R212.2, R213.2, R214.2, R216.2, R217.2, R218.2, R219.2, R457.2, R458.2; also elsewhere on the board
B5_2: Q383.G, Q385.D, R214.1, R215.1
B5_2_N: Q384.D, Q385.G, Q395.G, R213.1
B5_3: Q391.G, Q393.D, R219.1, R220.1
B5_3_N: Q392.D, Q393.G, Q396.G, R218.1
BSEL5_N: Q728.G, Q729.G; also elsewhere on the board
GND: Q379.S, Q381.S, Q383.S, Q386.S, Q387.S, Q389.S, Q391.S, Q394.S, Q395.S, Q396.S, Q728.S, Q729.S; also elsewhere on the board
unnamed: Q379.D, Q380.S
unnamed: Q381.D, Q382.S
unnamed: Q383.D, Q384.S
unnamed: Q380.D, Q382.G, Q384.G, R211.1
unnamed: Q382.D, Q386.G, R212.1
unnamed: D43.K (C), R215.2
unnamed: Q385.S, Q386.D
unnamed: Q387.D, Q388.S
unnamed: Q389.D, Q390.S
unnamed: Q391.D, Q392.S
unnamed: Q388.D, Q390.G, Q392.G, R216.1
unnamed: Q390.D, Q394.G, R217.1
unnamed: D44.K (C), R220.2
unnamed: Q393.S, Q394.D
RD_5_2: Q395.D, Q728.D, R457.1; also elsewhere on the board
RD_5_3: Q396.D, Q729.D, R458.1; also elsewhere on the board
WD2: Q380.G; also elsewhere on the board
WD3: Q388.G; also elsewhere on the board
WR_BYTE5: Q379.G, Q381.G, Q387.G, Q389.G; also elsewhere on the board

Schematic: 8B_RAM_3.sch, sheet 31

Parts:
D45, D46: L-1334SRT; LED3MM
Q397, Q398, Q399, Q400, Q401, Q402, Q403, Q404, Q405, Q406, Q407, Q408, Q409, Q410, Q411, Q412, Q413, Q414, Q730, Q731: 2N7000; TO92-DGS
R221, R222, R223, R224, R226, R227, R228, R229, R459, R460: 10k; R_P2INCH
R225, R230: 470; R_P2INCH

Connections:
+5V: D45.A, D46.A, R221.2, R222.2, R223.2, R224.2, R226.2, R227.2, R228.2, R229.2, R459.2, R460.2; also elsewhere on the board
B5_4: Q401.G, Q403.D, R224.1, R225.1
B5_4_N: Q402.D, Q403.G, Q413.G, R223.1
B5_5: Q409.G, Q411.D, R229.1, R230.1
B5_5_N: Q410.D, Q411.G, Q414.G, R228.1
BSEL5_N: Q730.G, Q731.G; also elsewhere on the board
GND: Q397.S, Q399.S, Q401.S, Q404.S, Q405.S, Q407.S, Q409.S, Q412.S, Q413.S, Q414.S, Q730.S, Q731.S; also elsewhere on the board
unnamed: Q397.D, Q398.S
unnamed: Q399.D, Q400.S
unnamed: Q401.D, Q402.S
unnamed: Q398.D, Q400.G, Q402.G, R221.1
unnamed: Q400.D, Q404.G, R222.1
unnamed: D45.K (C), R225.2
unnamed: Q403.S, Q404.D
unnamed: Q405.D, Q406.S
unnamed: Q407.D, Q408.S
unnamed: Q409.D, Q410.S
unnamed: Q406.D, Q408.G, Q410.G, R226.1
unnamed: Q408.D, Q412.G, R227.1
unnamed: D46.K (C), R230.2
unnamed: Q411.S, Q412.D
RD_5_4: Q413.D, Q730.D, R459.1; also elsewhere on the board
RD_5_5: Q414.D, Q731.D, R460.1; also elsewhere on the board
WD4: Q398.G; also elsewhere on the board
WD5: Q406.G; also elsewhere on the board
WR_BYTE5: Q397.G, Q399.G, Q405.G, Q407.G; also elsewhere on the board

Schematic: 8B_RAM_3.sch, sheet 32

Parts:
D47, D48: L-1334SRT; LED3MM
Q415, Q416, Q417, Q418, Q419, Q420, Q421, Q422, Q423, Q424, Q425, Q426, Q427, Q428, Q429, Q430, Q431, Q432, Q732, Q733: 2N7000; TO92-DGS
R231, R232, R233, R234, R236, R237, R238, R239, R461, R462: 10k; R_P2INCH
R235, R240: 470; R_P2INCH

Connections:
+5V: D47.A, D48.A, R231.2, R232.2, R233.2, R234.2, R236.2, R237.2, R238.2, R239.2, R461.2, R462.2; also elsewhere on the board
B5_6: Q419.G, Q421.D, R234.1, R235.1
B5_6_N: Q420.D, Q421.G, Q431.G, R233.1
B5_7: Q427.G, Q429.D, R239.1, R240.1
B5_7_N: Q428.D, Q429.G, Q432.G, R238.1
BSEL5_N: Q732.G, Q733.G; also elsewhere on the board
GND: Q415.S, Q417.S, Q419.S, Q422.S, Q423.S, Q425.S, Q427.S, Q430.S, Q431.S, Q432.S, Q732.S, Q733.S; also elsewhere on the board
unnamed: Q415.D, Q416.S
unnamed: Q417.D, Q418.S
unnamed: Q419.D, Q420.S
unnamed: Q416.D, Q418.G, Q420.G, R231.1
unnamed: Q418.D, Q422.G, R232.1
unnamed: D47.K (C), R235.2
unnamed: Q421.S, Q422.D
unnamed: Q423.D, Q424.S
unnamed: Q425.D, Q426.S
unnamed: Q427.D, Q428.S
unnamed: Q424.D, Q426.G, Q428.G, R236.1
unnamed: Q426.D, Q430.G, R237.1
unnamed: D48.K (C), R240.2
unnamed: Q429.S, Q430.D
RD_5_6: Q431.D, Q732.D, R461.1; also elsewhere on the board
RD_5_7: Q432.D, Q733.D, R462.1; also elsewhere on the board
WD6: Q416.G; also elsewhere on the board
WD7: Q424.G; also elsewhere on the board
WR_BYTE5: Q415.G, Q417.G, Q423.G, Q425.G; also elsewhere on the board
